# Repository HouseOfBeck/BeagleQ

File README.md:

BeagleQ bbq controller based on the beaglebone black platform.

Big changes for new Version 3.  New Version 3 board. Built in DC power converter. New form factor to fit off the shelf case.

The BeagleQ is a wifi enabled wireless intelligent bbq smoker controller. This device is designed to control a fan connected to the smoker's input vent/damper. Using a temperature probe placed in the pit the controller can read the pit temperature and then adjust the fan speed to act as a bellows to cause the coals to heat up and raise the pit temperature. The fan shuts down when the desired temperature is reached. By continually monitoring the temperature and adjusting the fan speed the controller can insure a smooth low and slow cook.

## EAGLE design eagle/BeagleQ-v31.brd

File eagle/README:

I've had a batch of these boards build at OSH Park and they work fine.
There's one minor issue. One mounting hole on the headphone/RCA jacks is a wee bit to small.
A little touch of the dremel on the pin and it fits in just fine.

Functionally I'm happy with this board and will use it as the basis for my
software developement.

You can order these boards from OSH Park here

http://www.oshpark.com/shared_projects/zo1bDKMN

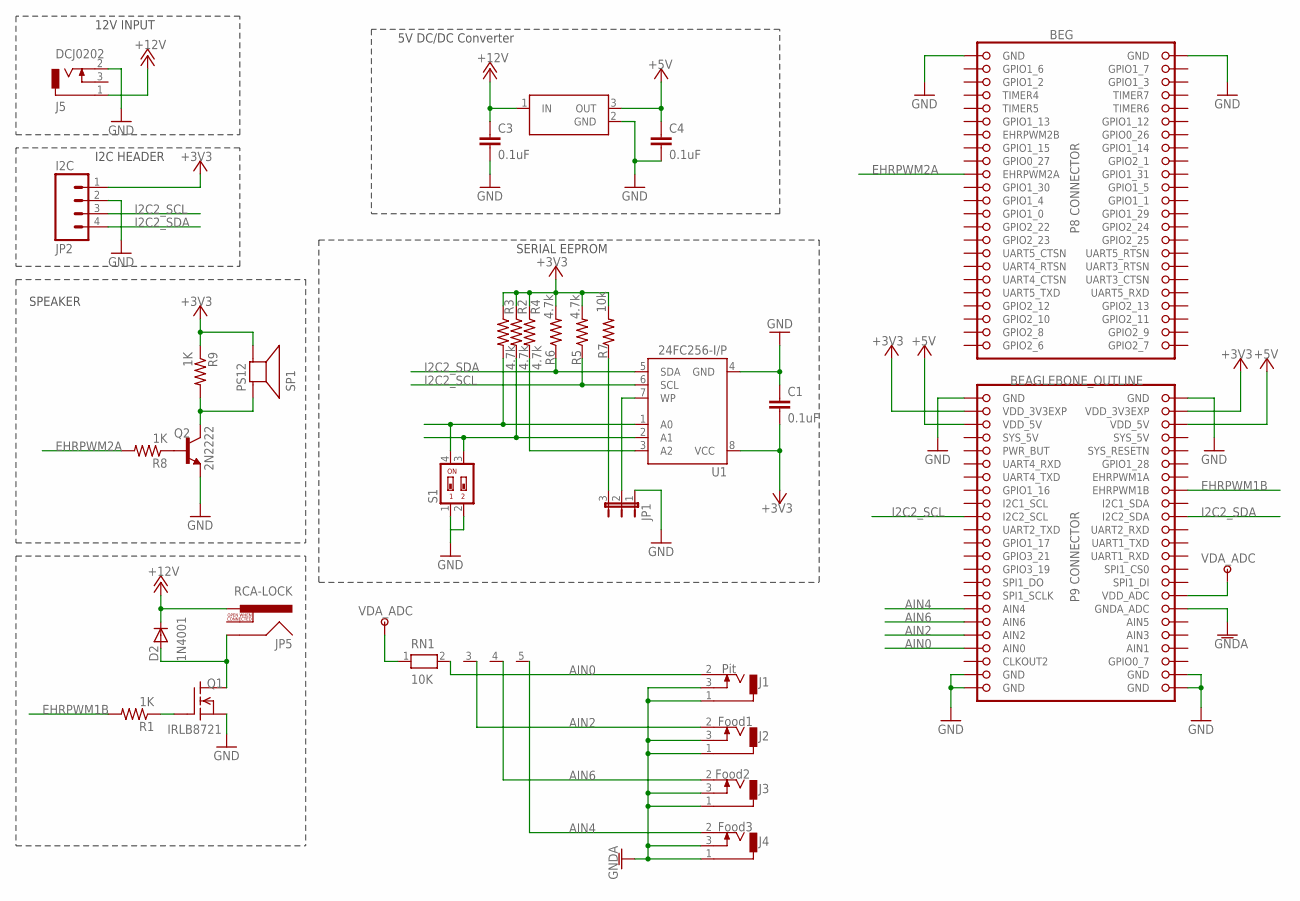
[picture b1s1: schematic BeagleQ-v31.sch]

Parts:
BEG: BEAGLEBONE_OUTLINE; BEAGLEBONE_SHIELD
C1, C3, C4: 0.1uF; C2.5-2
D2: 1N4001; DO41-10
J1: Pit; MJ-2508N
J2: Food1; MJ-2508N
J3: Food2; MJ-2508N
J4: Food3; MJ-2508N
J5: DCJ0202
JP1: WP; JP2
JP2: I2C; 1X04
JP5: RCA-LOCK; RCA_LOCK
Q1: IRLB8721; TO220
Q2: 2N2222; TO-92
R1, R8, R9: 1K; 0207/10
R2, R3, R4, R5, R6: 4.7k; 0207/10
R7: 10k; 0207/10
RN1: 10K; RN-5
S1: SWS002; SMS-002
SP1: PS12
U1: 24FC256-I/P; DIL08
U2: OKI-78SRHZNTL; OKI-78SR-HZNTL

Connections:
+3V3: BEG.49 (VDD_3V3EXP), BEG.50 (VDD_3V3EXP), C1.2, JP2.1, R2.1, R3.1, R4.1, R5.2, R6.2, R7.2, R9.1, SP1.P$2 (-), U1.8 (VCC)
+5V: BEG.51 (VDD_5V), BEG.52 (VDD_5V), C4.1, U2.3 (OUT)
+12V: C3.1, D2.C, J5.1, JP5.PIN, U2.1 (IN)
AIN0: BEG.85 (AIN0), J1.2, RN1.2
AIN2: BEG.83 (AIN2), J2.2, RN1.3
AIN4: BEG.79 (AIN4), J4.2, RN1.5
AIN6: BEG.81 (AIN6), J3.2, RN1.4
BLOWER_L: D2.A, JP5.SHELL, Q1.2 (D)
EHRPWM1B: BEG.62 (EHRPWM1B), R1.2
EHRPWM2A: BEG.19 (EHRPWM2A), R8.2
GND: BEG.1 (GND), BEG.2 (GND), BEG.47 (GND), BEG.48 (GND), BEG.89 (GND), BEG.90 (GND), BEG.91 (GND), BEG.92 (GND), C1.1, C3.2, C4.2, J5.2 (3), JP1.1, JP2.2, Q1.3 (S), Q1.4 (S), Q2.1 (E), S1.1, S1.2, U1.4 (GND), U2.2 (GND)
GNDA: BEG.80 (GNDA_ADC), J1.1, J1.3, J2.1, J2.3, J3.1, J3.3, J4.1, J4.3
I2C2_SCL: BEG.65 (I2C2_SCL), JP2.3, R5.1, U1.6 (SCL)
I2C2_SDA: BEG.66 (I2C2_SDA), JP2.4, R6.1, U1.5 (SDA)
unnamed: R2.2, S1.3, U1.2 (A1)
unnamed: R3.2, S1.4, U1.1 (A0)
unnamed: JP1.2, U1.7 (WP)
unnamed: Q1.1 (G), R1.1
unnamed: JP1.3, R7.1
unnamed: R4.2, U1.3 (A2)
unnamed: Q2.2 (B), R8.1
unnamed: Q2.3 (C), R9.2, SP1.P$1 (+)
SYS_5V: BEG.53 (SYS_5V)
VDA_ADC: BEG.78 (VDD_ADC), RN1.1

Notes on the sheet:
12V INPUT
I2C HEADER
SERIAL EEPROM
5V DC/DC Converter
SPEAKER

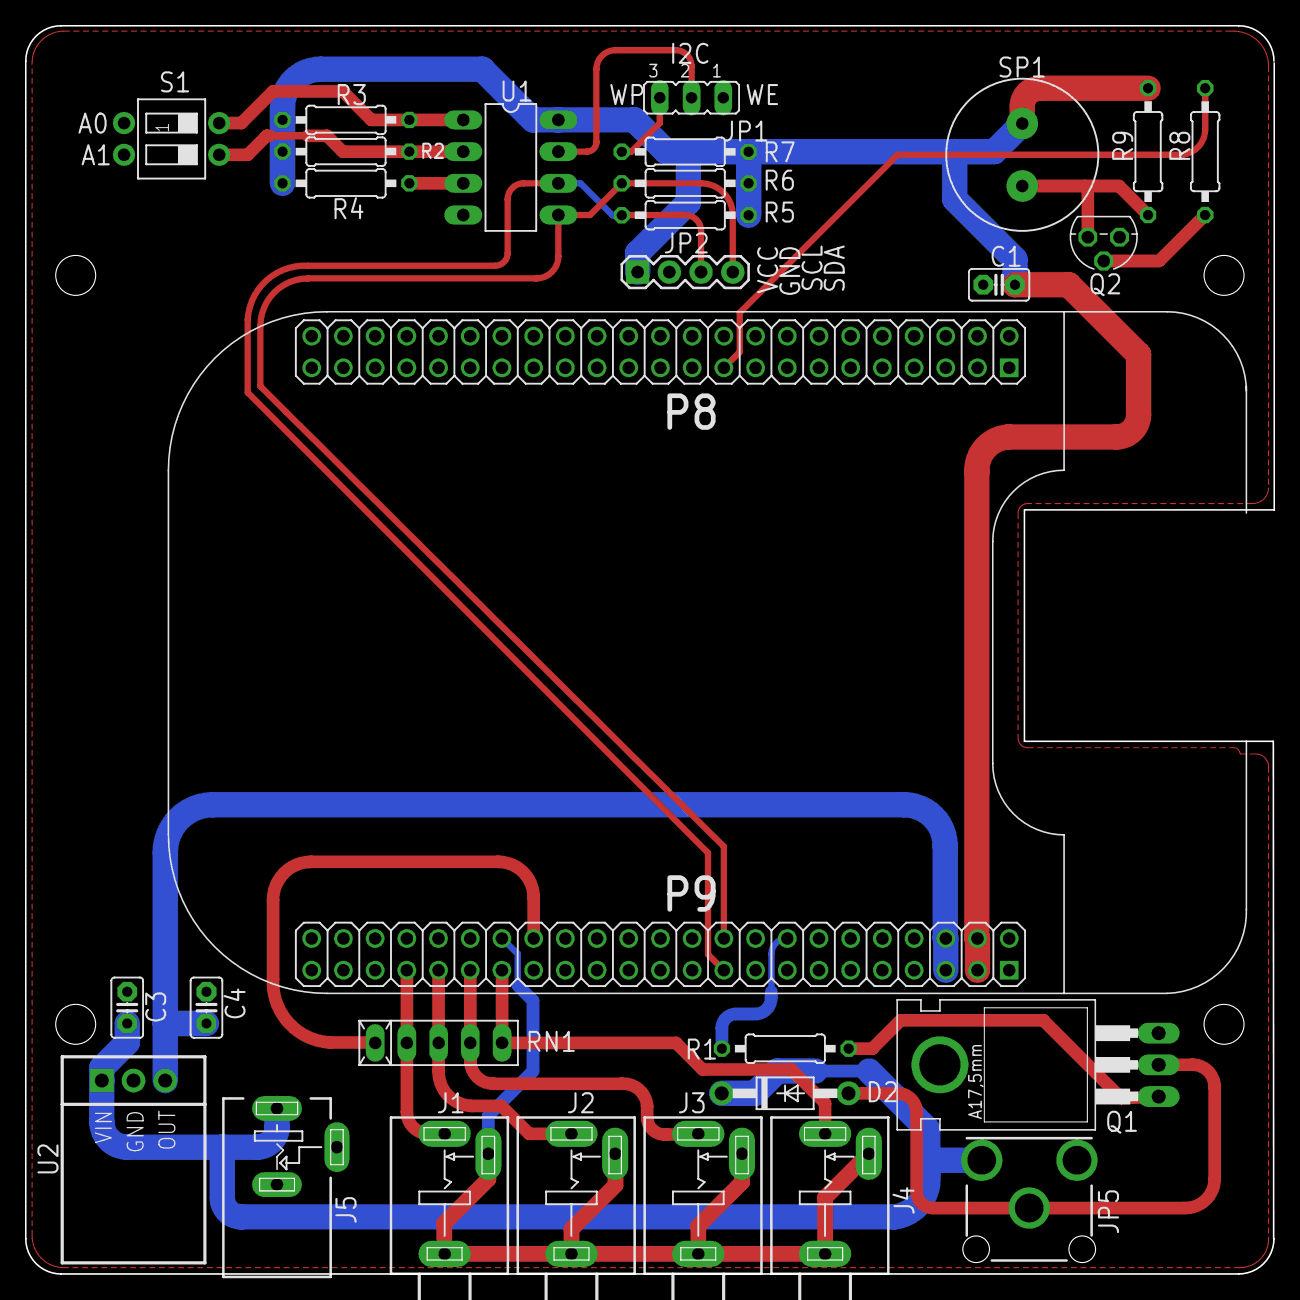
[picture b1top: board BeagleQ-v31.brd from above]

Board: 2 copper layers, 100.0 x 100.0 mm, 29 parts (0 on the bottom side), 23 nets.

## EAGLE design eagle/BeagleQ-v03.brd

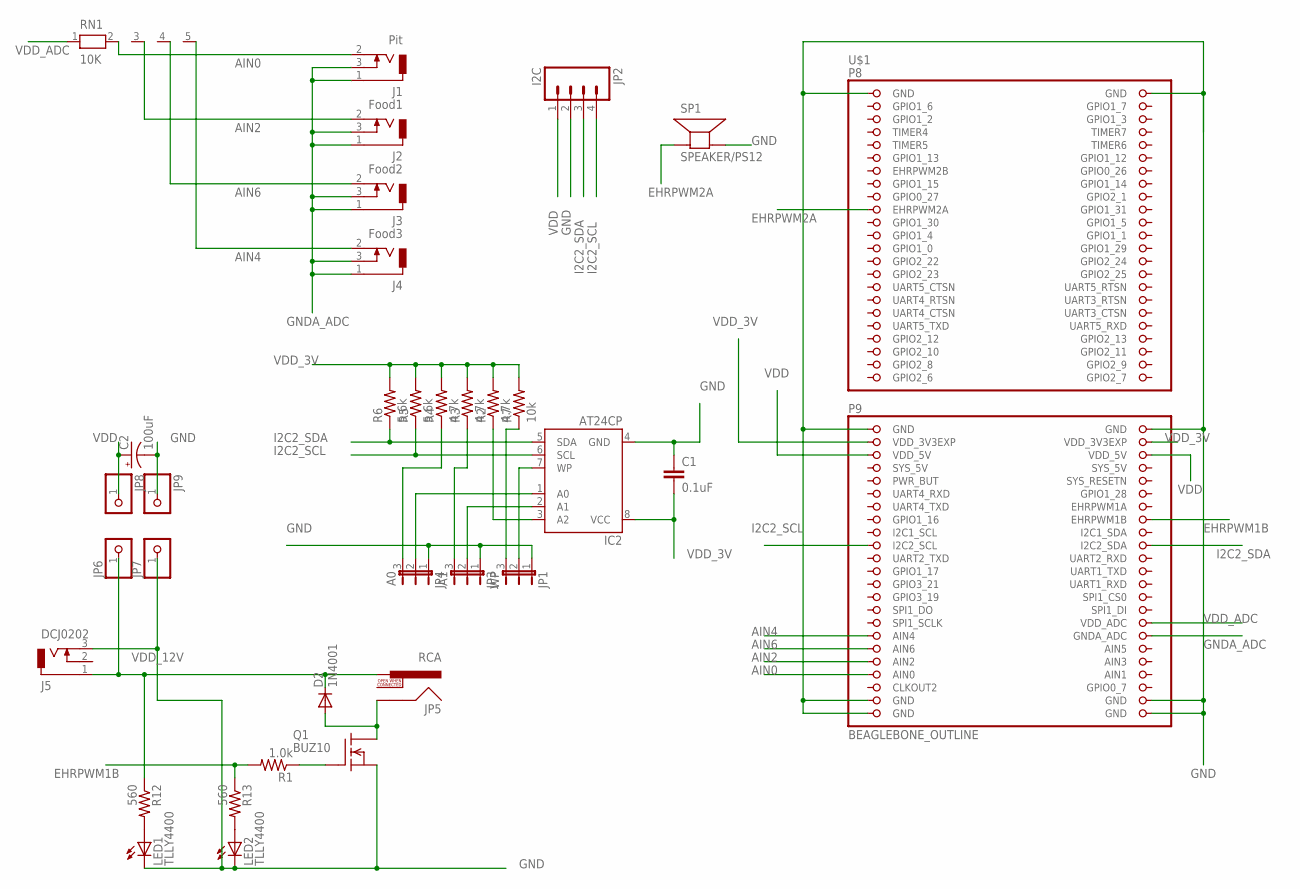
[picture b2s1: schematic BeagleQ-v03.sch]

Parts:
C1: 0.1uF; C2.5-2
C2: 100uF; E2,5-6E
D2: 1N4001; DO41-10
IC2: AT24CP; DIL08
J1: Pit; DCJ0202
J2: Food1; DCJ0202
J3: Food2; DCJ0202
J4: Food3; DCJ0202
J5: DCJ0202
JP1: WP; JP2
JP2: I2C; 1X04
JP3: A1; JP2
JP4: A0; JP2
JP5: RCA
JP6, JP7, JP8, JP9: PINHD-1X1; 1X01
LED1, LED2: TLLY4400; LED3MM
Q1: BUZ10; TO220
R1: 1.0k; 0207/10
R2, R3, R4: 4.7k; 0207/10
R5, R6: 5.6k; 0207/10
R7: 10k; 0207/10
R12, R13: 560; 0207/10
RN1: 10K; RN-5
SP1: SPEAKER/PS12; PS12
U$1: BEAGLEBONE_OUTLINE; BEAGLEBONE_SHIELD

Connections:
AIN0: J1.2, RN1.2, U$1.85 (AIN0)
AIN2: J2.2, RN1.3, U$1.83 (AIN2)
AIN4: J4.2, RN1.5, U$1.79 (AIN4)
AIN6: J3.2, RN1.4, U$1.81 (AIN6)
BLOWER_L: D2.A, JP5.SHELL, Q1.2 (D)
EHRPWM1B: R1.2, R13.1, U$1.62 (EHRPWM1B)
EHRPWM2A: SP1.P$1 (+), U$1.19 (EHRPWM2A)
GND: C1.1, C2.-, IC2.4 (GND), J5.3, JP1.1, JP2.2, JP3.1, JP4.1, JP7.1, JP9.1, LED1.K (C), LED2.K (C), Q1.3 (S), SP1.P$2 (-), U$1.1 (GND), U$1.2 (GND), U$1.47 (GND), U$1.48 (GND), U$1.89 (GND), U$1.90 (GND), U$1.91 (GND), U$1.92 (GND)
GNDA_ADC: J1.1, J1.3, J2.1, J2.3, J3.1, J3.3, J4.1, J4.3, U$1.80 (GNDA_ADC)
I2C2_SCL: IC2.6 (SCL), JP2.4, R5.1, U$1.65 (I2C2_SCL)
I2C2_SDA: IC2.5 (SDA), JP2.3, R6.1, U$1.66 (I2C2_SDA)
unnamed: IC2.2 (A1), JP3.2
unnamed: IC2.1 (A0), JP4.2
unnamed: IC2.7 (WP), JP1.2
unnamed: Q1.1 (G), R1.1
unnamed: JP1.3, R7.1
unnamed: JP3.3, R3.1
unnamed: JP4.3, R4.1
unnamed: LED1.A, R12.2
unnamed: IC2.3 (A2), R2.1
unnamed: LED2.A, R13.2
SYS_5V: U$1.53 (SYS_5V)
VDD: C2.+, JP2.1, JP8.1, U$1.51 (VDD_5V), U$1.52 (VDD_5V)
VDD_3V: C1.2, IC2.8 (VCC), R2.2, R3.2, R4.2, R5.2, R6.2, R7.2, U$1.49 (VDD_3V3EXP), U$1.50 (VDD_3V3EXP)
VDD_12V: D2.C, J5.1, JP5.PIN, JP6.1, R12.1
VDD_ADC: RN1.1, U$1.78 (VDD_ADC)

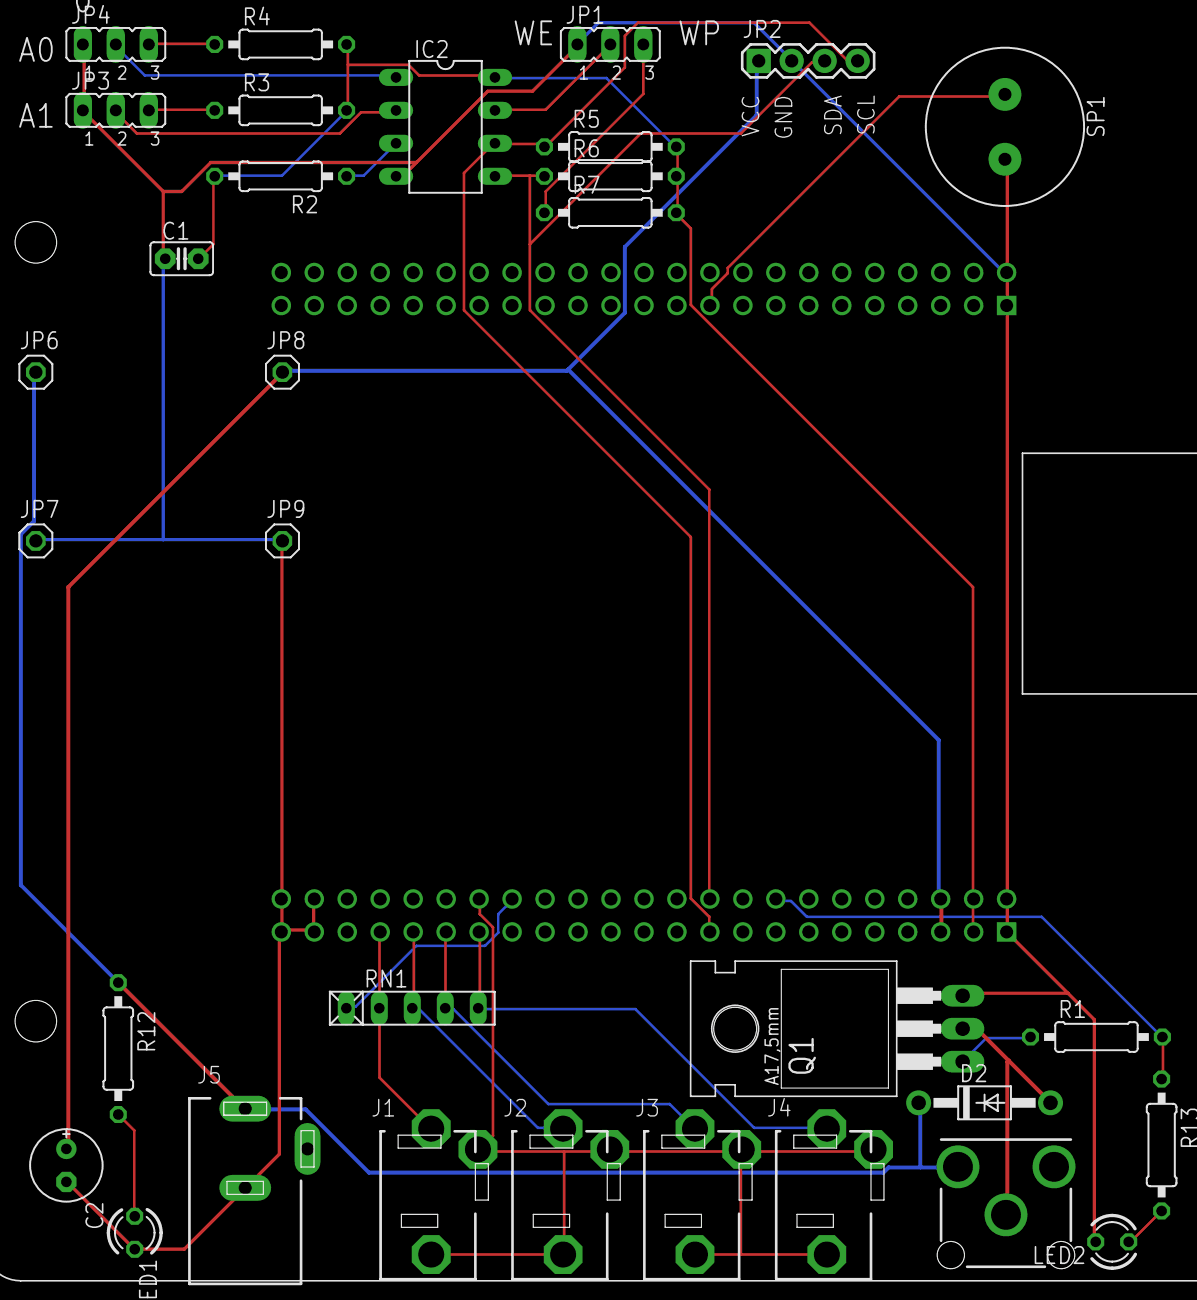
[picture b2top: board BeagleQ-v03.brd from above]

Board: 2 copper layers, 33 parts (0 on the bottom side), 25 nets.

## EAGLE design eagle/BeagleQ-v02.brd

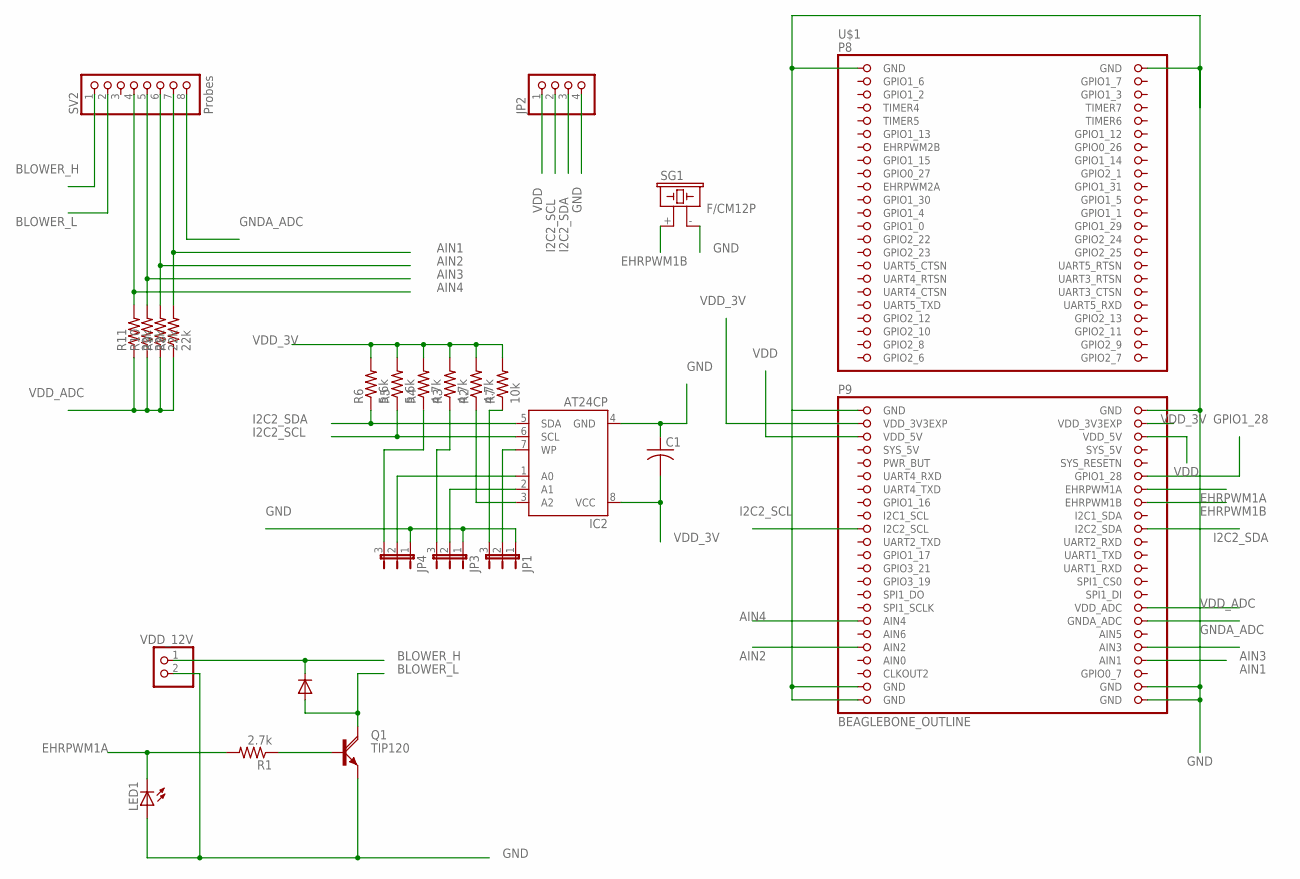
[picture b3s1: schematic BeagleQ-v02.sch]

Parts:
C1: C-US025-025X050; C025-025X050
IC2: AT24CP; DIL08
JP1, JP3, JP4: JP2E; JP2
JP2: PINHD-1X4/90; 1X04/90
LED1: LED3MM
Q1: TIP120; TO220AH
R1: 2.7k; 0207/10
R2, R3, R4: 4.7k; 0207/10
R5, R6: 5.6k; 0207/10
R7: 10k; 0207/10
R8, R9, R10, R11: 22k; 0207/10
SG1: F/CM12P
SV2: Probes; 1X08/90
U$1: BEAGLEBONE_OUTLINE; BEAGLEBONE_SHIELD
VDD_12V: PINHD-1X2/90; 1X02/90

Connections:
AIN0: U$1.85 (AIN0)
AIN1: R8.2, SV2.7, U$1.86 (AIN1)
AIN2: R9.2, SV2.6, U$1.83 (AIN2)
AIN3: R10.2, SV2.5, U$1.84 (AIN3)
AIN4: R11.2, SV2.4, U$1.79 (AIN4)
BLOWER_H: SV2.1, VDD_12V.1
BLOWER_L: Q1.C, SV2.2
EHRPWM1A: LED1.K (C), R1.2, U$1.60 (EHRPWM1A)
EHRPWM1B: SG1.+ (1), U$1.62 (EHRPWM1B)
GND: C1.1, IC2.4 (GND), JP1.1, JP2.4, JP3.1, JP4.1, LED1.A, Q1.E, SG1.- (2), U$1.1 (GND), U$1.2 (GND), U$1.47 (GND), U$1.48 (GND), U$1.89 (GND), U$1.90 (GND), U$1.91 (GND), U$1.92 (GND), VDD_12V.2
GNDA_ADC: SV2.8, U$1.80 (GNDA_ADC)
GPIO1_28: U$1.58 (GPIO1_28)
I2C2_SCL: IC2.6 (SCL), JP2.2, R5.1, U$1.65 (I2C2_SCL)
I2C2_SDA: IC2.5 (SDA), JP2.3, R6.1, U$1.66 (I2C2_SDA)
unnamed: IC2.2 (A1), JP3.2
unnamed: IC2.1 (A0), JP4.2
unnamed: IC2.7 (WP), JP1.2
unnamed: Q1.B, R1.1
unnamed: JP1.3, R7.1
unnamed: JP3.3, R3.1
unnamed: JP4.3, R4.1
unnamed: IC2.3 (A2), R2.1
SYS_5V: U$1.53 (SYS_5V)
VDD: JP2.1, U$1.51 (VDD_5V), U$1.52 (VDD_5V)
VDD_3V: C1.2, IC2.8 (VCC), R2.2, R3.2, R4.2, R5.2, R6.2, R7.2, U$1.49 (VDD_3V3EXP), U$1.50 (VDD_3V3EXP)
VDD_ADC: R8.1, R9.1, R10.1, R11.1, U$1.78 (VDD_ADC)

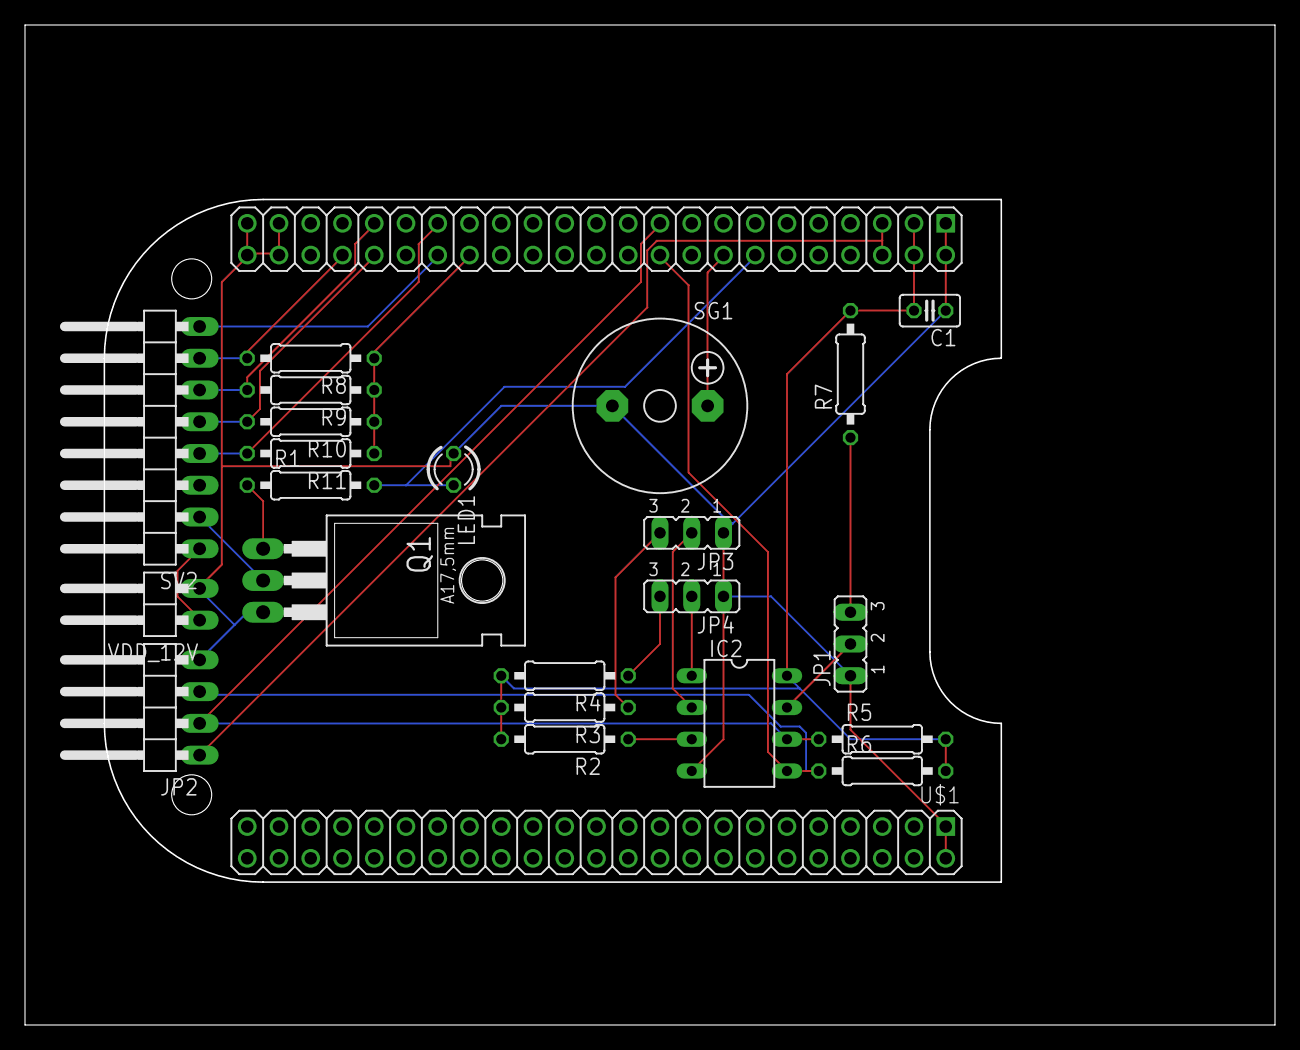
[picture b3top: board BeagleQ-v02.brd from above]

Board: 2 copper layers, 100.0 x 80.0 mm, 23 parts (0 on the bottom side), 23 nets.

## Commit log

2013-10-02 Eagle Files
2013-10-03 Added reality
2013-10-16 Initial port to BBB
2013-10-16 commit all
2013-10-16 cleaning up mess
2013-11-24 Functioning hardware
2013-11-24 Fixed eeprom README
2013-11-24 Added images
2013-11-25 README updates
2014-02-16 web server and client
2014-02-16 more board pictures
2014-02-16 screenshots
2014-02-16 removed typos
2014-02-16 Update parts
2014-02-26 better description
2014-06-29 Version3
2014-07-11 Added Screen shots
2014-07-11 Added support for Adafruit i2c 7-segment display
2014-08-19 Major Cleanup
2014-12-20 Minor Cleanup
2014-12-27 Updated pictures
2014-12-27 Connect picture
2014-12-28 Parts List

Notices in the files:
parts and their libraries:
SparkFun-Connectors: Licensing: CC v3.0 Share-Alike You are welcome to use this library for commercial purposes.
